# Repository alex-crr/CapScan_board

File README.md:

# CapScan 5x5

Bench readout board that scans a 5 TX x 5 RX printed skin sensor (reSkin / Skin-On) and returns the mutual capacitance of each taxel in pF. Sibling of [Muca_board](../Muca_board) (MUCA2), which returns raw FocalTech counts.

Status: rev 0.1. Schematic complete (ERC 0 errors). Board placed and fully routed (35/35 nets, KiCadRoutingTools checker: 0 violations, all nets connected). Still to do in KiCad: fill the B.Cu GND zone (press B), run KiCad's own DRC, silkscreen. Not fabricated.

## How it measures

One taxel at a time: the selected TX line is connected to the AD7746 excitation output (EXCA), the selected RX line to its input (CIN1+), and the 8 other lines are grounded. The AD7746 measures the floating capacitance between EXC and CIN; capacitance to ground is rejected (up to its 60 pF limit), so the grounded neighbours do not add to the reading.

| Block | Part | Notes |
|---|---|---|
| CDC | AD7746ARUZ (TSSOP-16) | 24-bit, +/-4.096 pF span around a CAPDAC offset of 0 to 17 pF, 11 to 109 ms per conversion, I2C 0x48. Internal reference; REFIN, VIN, CIN1-, CIN2, EXCB unused. |
| Line switches | 10x 74LVC1G3157 (SC-70-6) | One SPDT per line: B0 -> bus (EXC or CIN), B1 -> GND. |
| Reference | C8 2.2 pF C0G +/-0.05 pF (0402) + U14 74LVC1G3157 | C8 sits between EXC and CIN through its own switch, selected by IO1_5 (active low). Same bus and switch type as a taxel, so it checks gain including the CIN loading. |
| Select | PCA9555PW (TSSOP-24) | I2C 0x20. IO0_0-4 = TX1-5, IO1_0-4 = RX1-5, IO1_5 = reference. Select is active LOW. Power-up state is input with internal pull-up, so all lines are grounded until the firmware selects one. |
| Host | Seeed XIAO ESP32S3 (SMD) | USB-C and 3.3 V regulator on the module. |
| Power | XIAO 3V3 -> ferrite -> +3.3VA | +3.3VA feeds the AD7746 and the switches. |
| Sensor I/O | 2x 2.54 mm right-angle socket, 1x5 | J1 TX1-5, J2 RX1-5, same Clincher tail as MUCA2. |
| Grounding | H4 | Plated M3 hole on GND for a shield or the test fixture. H1-H3 are unplated. |
| Debug | PWR, HB, SENSE LEDs, 4-pin I2C header | J3: 3V3, GND, SDA, SCL. |

## XIAO pin map

| XIAO pin | GPIO | Function |
|---|---|---|
| D0 | GPIO1 | CDC_RDY (low when a conversion is ready) |
| D4 / D5 | GPIO5 / GPIO6 | SDA / SCL (default `Wire` pins), 2.2 kohm pull-ups |
| D8 / D9 | GPIO7 / GPIO8 | LED_HB / LED_SENSE (active high) |

## Scan sequence (firmware)

1. PCA9555: write output registers to 0xFF, then configure IO0_0-4 and IO1_0-5 as outputs.
2. For each taxel: clear the TX bit and the RX bit, wait about 1 ms, start a single conversion, wait for CDC_RDY, read 24 bits, set the two bits again.
3. C[pF] = (code - 0x800000) / 0x800000 * 4.096 + CAPDAC offset.

4. Calibration: with nothing selected, read the zero (board stray). Then clear only IO1_5 and read the reference: gain = C8 / (reference - zero). Repeat at the start of each session and when temperature changes.

A full 25-taxel frame takes about 0.3 s at the fastest setting and about 2.7 s at the lowest-noise one.

## Layout

48 x 47 mm, 2 layers, all parts on top, symmetric about the centre line. Top to bottom: sensor sockets (RX left, TX right), one switch directly under each socket pin with its row decoupling at both ends, AD7746 on the centre line between the two rows (CIN and EXC buses a few mm long), PCA9555 under the TX row, XIAO on the bottom edge with USB facing out, LEDs left of it and the I2C header right. The area under the RX row is left empty on purpose: it is the quiet zone around CIN.

## Open points

- Routing: sensor lines, GND vias, CIN/EXC buses and the reference branch are hand-laid (`tools/prelay.py`); the rest is autorouted with KiCadRoutingTools 0.24 (track 0.2 mm, power 0.3 mm, via 0.6/0.3 mm, clearance 0.15 mm requested, 0.144 mm minimum delivered, no via-in-pad). The autorouted part is functional, not pretty: the RX select lines cross the empty zone under the RX row on F.Cu, and select lines and +3.3VA cut the B.Cu plane in places.
- Rebuild order if the placement changes: `tools/place.py`, strip copper, `tools/prelay.py`, then route_planes.py (GND on B.Cu) and route.py with --keep-input-copper.
- CIN node capacitance to ground: about 18 pF (one switch on) + 5 x 6 pF (switches off) + traces + the sensor RX line to the grounded TX lines. The AD7746 limit is 60 pF. The switch values are from memory of the Nexperia datasheet: check them, and measure the gain error with a known C0G capacitor on a socket.
- C8 gives a repeatable reference, not a traceable one: its tolerance is 0.05 pF but the pads and the switch add stray of the same order. For absolute values, measure C8 in place once with an LCR meter (or compare with a known external C0G on a socket) and store that number.
- Taxel capacitance above 21 pF (17 pF CAPDAC + 4 pF) is out of range without the range-extension circuit of ADI CN-0552.
- No CAN (bench instrument). Add the MUCA2 CAN sheet if it has to go on a prosthesis.
- Silkscreen, 3D check of socket direction.

## Files

- `CapScan5x5.kicad_pro` - project (single A3 sheet)
- `CapScan.kicad_sym`, `CapScan.pretty/` - XIAO ESP32S3 symbol and footprint (copied from MUCA2)
- `tools/build_sch.py` - regenerates the schematic wiring and layout from `tools/base.placed` (run from this folder). Delete `tools/` once the schematic is edited by hand.

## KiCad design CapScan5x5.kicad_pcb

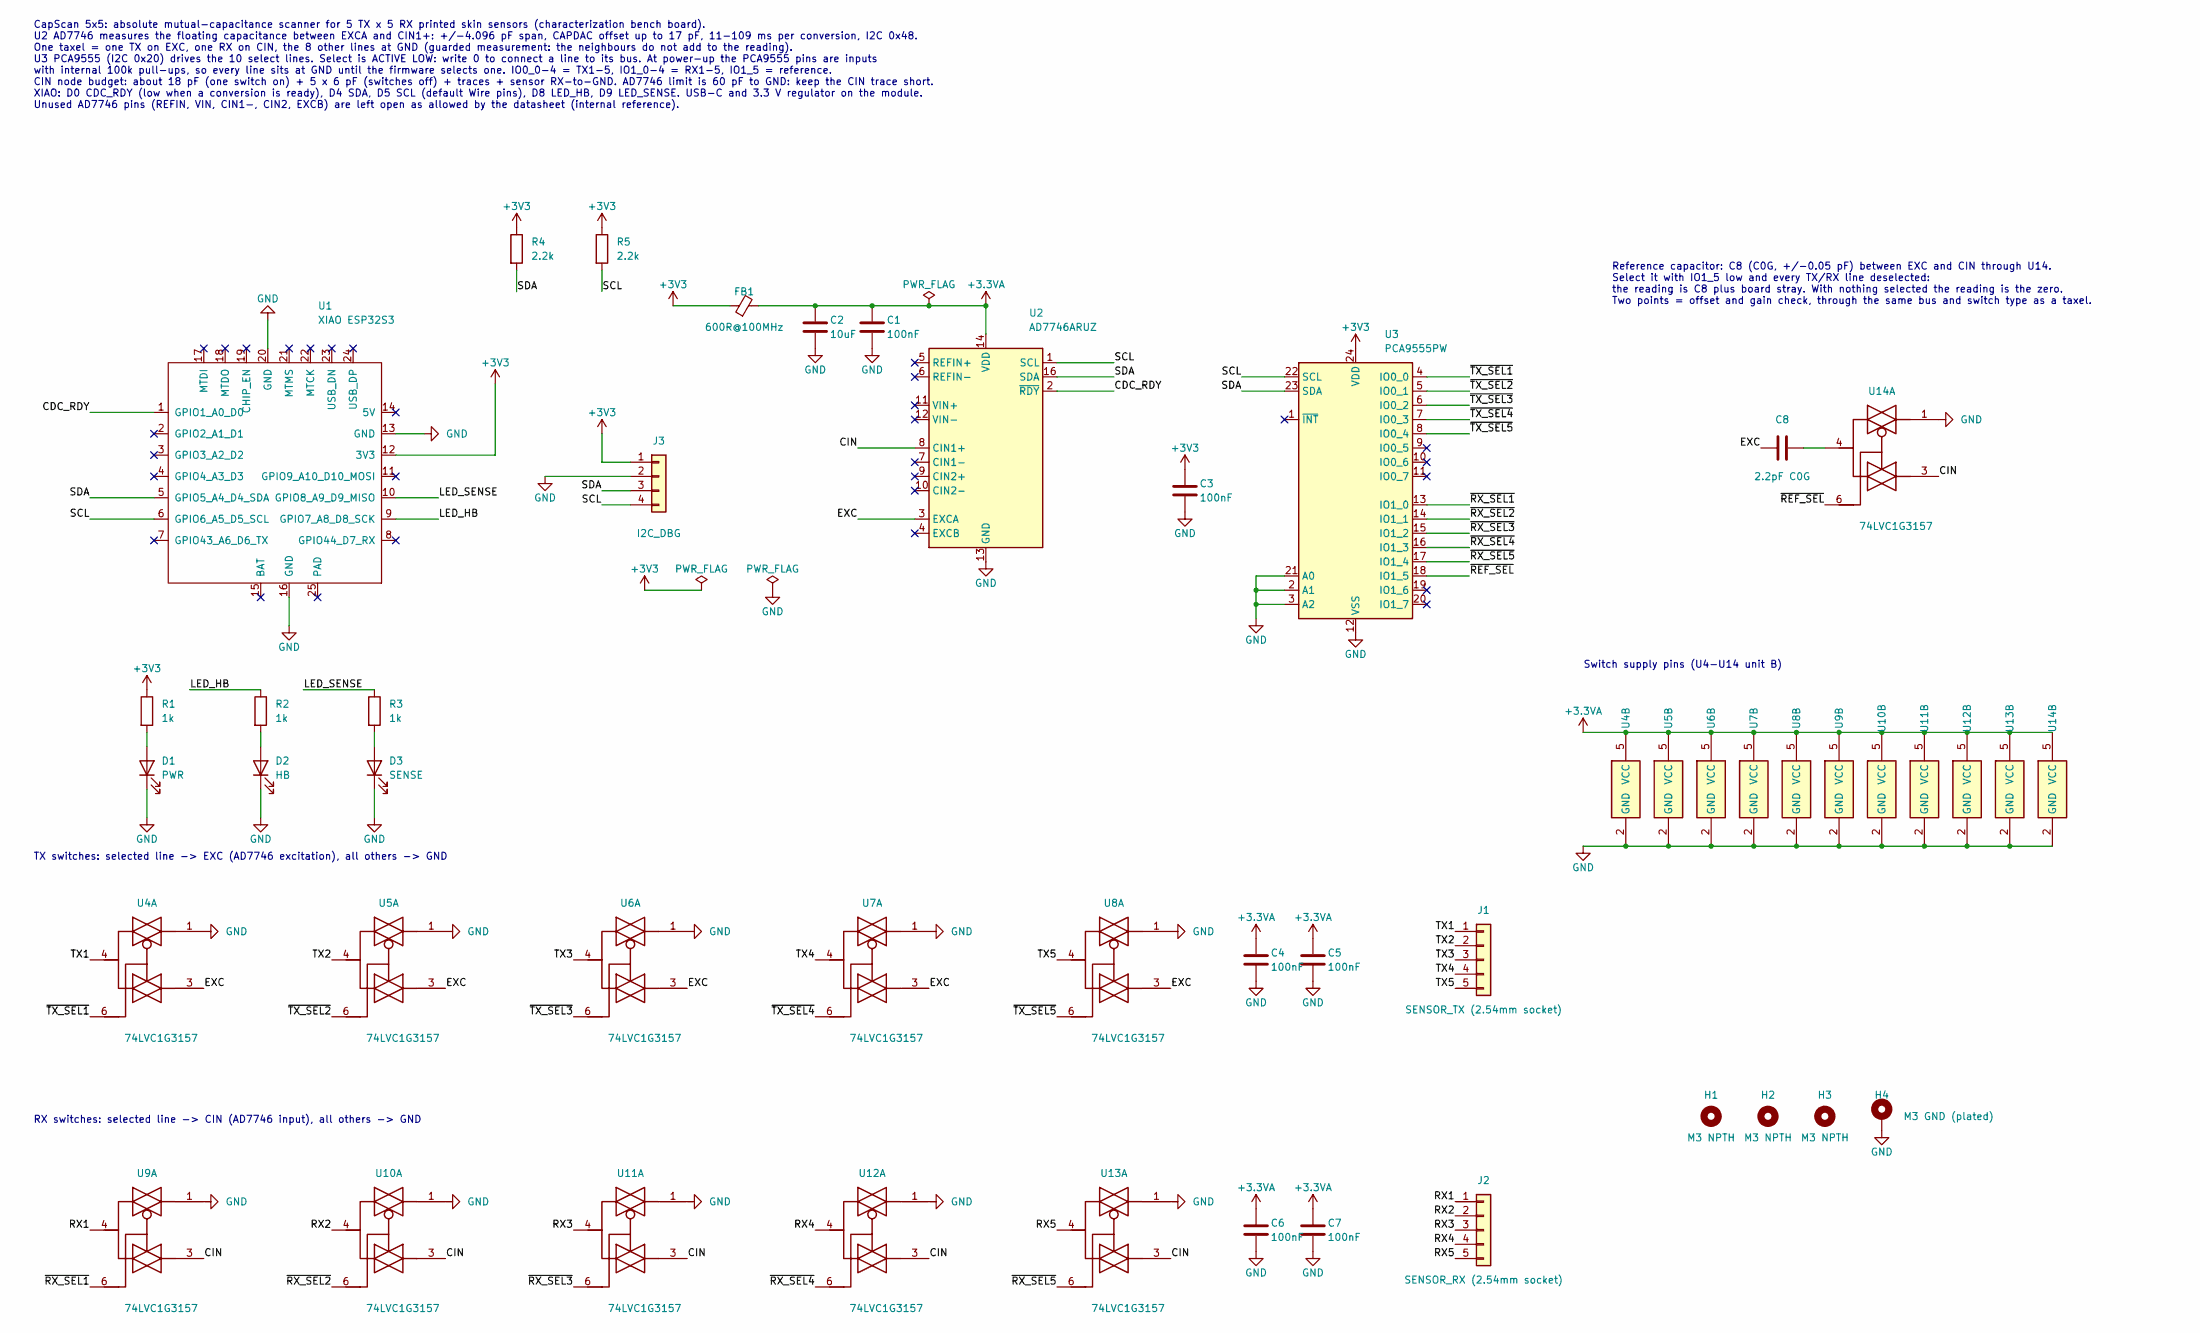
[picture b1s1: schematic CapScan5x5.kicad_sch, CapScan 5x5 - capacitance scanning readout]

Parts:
C1, C3, C4, C5, C6, C7: 100nF; C_0402_1005Metric
C2: 10uF; C_0603_1608Metric
C8: 2.2pF C0G; C_0402_1005Metric
D1: PWR; LED_0603_1608Metric
D2: HB; LED_0603_1608Metric
D3: SENSE; LED_0603_1608Metric
FB1: 600R@100MHz; L_0603_1608Metric
H1, H2, H3: M3 NPTH; MountingHole_3.2mm_M3
H4: M3 GND (plated); MountingHole_3.2mm_M3_Pad
J1: SENSOR_TX (2.54mm socket); PinSocket_1x05_P2.54mm_Horizontal
J2: SENSOR_RX (2.54mm socket); PinSocket_1x05_P2.54mm_Horizontal
J3: I2C_DBG; PinHeader_1x04_P2.54mm_Vertical
R1, R2, R3: 1k; R_0402_1005Metric
R4, R5: 2.2k; R_0402_1005Metric
U1: XIAO ESP32S3; XIAO-ESP32S3-SMD
U2: AD7746ARUZ; TSSOP-16_4.4x5mm_P0.65mm
U3: PCA9555PW; TSSOP-24_4.4x7.8mm_P0.65mm
U4, U5, U6, U7, U8, U9, U10, U11, U12, U13, U14: 74LVC1G3157; SOT-363_SC-70-6

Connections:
+3.3VA: C1.1, C2.1, C4.1, C5.1, C6.1, C7.1, FB1.2, U2.14 (VDD), U4.5 (VCC), U5.5 (VCC), U6.5 (VCC), U7.5 (VCC), U8.5 (VCC), U9.5 (VCC), U10.5 (VCC), U11.5 (VCC), U12.5 (VCC), U13.5 (VCC), U14.5 (VCC)
+3V3: C3.1, FB1.1, J3.1, R1.1, R4.1, R5.1, U1.12 (3V3), U3.24 (VDD)
CDC_RDY: U1.1 (GPIO1_A0_D0), U2.2 (~RDY)
CIN: U2.8 (CIN1+), U9.3, U10.3, U11.3, U12.3, U13.3, U14.3
EXC: C8.1, U2.3 (EXCA), U4.3, U5.3, U6.3, U7.3, U8.3
GND: C1.2, C2.2, C3.2, C4.2, C5.2, C6.2, C7.2, D1.1 (K), D2.1 (K), D3.1 (K), H4.1, J3.2, U1.13 (GND), U1.16 (GND), U1.20 (GND), U2.13 (GND), U3.2 (A1), U3.3 (A2), U3.12 (VSS), U3.21 (A0), U4.1, U4.2 (GND), U5.1, U5.2 (GND), U6.1, U6.2 (GND), U7.1, U7.2 (GND), U8.1, U8.2 (GND), U9.1, U9.2 (GND), U10.1, U10.2 (GND), U11.1, U11.2 (GND), U12.1, U12.2 (GND), U13.1, U13.2 (GND), U14.1, U14.2 (GND)
LED_HB: R2.1, U1.9 (GPIO7_A8_D8_SCK)
LED_SENSE: R3.1, U1.10 (GPIO8_A9_D9_MISO)
unnamed: C8.2, U14.4
unnamed: D1.2 (A), R1.2
unnamed: D2.2 (A), R2.2
unnamed: D3.2 (A), R3.2
RX1: J2.1, U9.4
RX2: J2.2, U10.4
RX3: J2.3, U11.4
RX4: J2.4, U12.4
RX5: J2.5, U13.4
SCL: J3.4, R5.2, U1.6 (GPIO6_A5_D5_SCL), U2.1 (SCL), U3.22 (SCL)
SDA: J3.3, R4.2, U1.5 (GPIO5_A4_D4_SDA), U2.16 (SDA), U3.23 (SDA)
TX1: J1.1, U4.4
TX2: J1.2, U5.4
TX3: J1.3, U6.4
TX4: J1.4, U7.4
TX5: J1.5, U8.4
~REF_SEL: U3.18 (IO1_5), U14.6
~RX_SEL1: U3.13 (IO1_0), U9.6
~RX_SEL2: U3.14 (IO1_1), U10.6
~RX_SEL3: U3.15 (IO1_2), U11.6
~RX_SEL4: U3.16 (IO1_3), U12.6
~RX_SEL5: U3.17 (IO1_4), U13.6
~TX_SEL1: U3.4 (IO0_0), U4.6
~TX_SEL2: U3.5 (IO0_1), U5.6
~TX_SEL3: U3.6 (IO0_2), U6.6
~TX_SEL4: U3.7 (IO0_3), U7.6
~TX_SEL5: U3.8 (IO0_4), U8.6

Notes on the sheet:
Switch supply pins (U4-U14 unit B)
Reference capacitor: C8 (C0G, +/-0.05 pF) between EXC and CIN through U14. Select it with IO1_5 low and every TX/RX line deselected: the reading is C8 plus board stray. With nothing selected the reading is the zero. Two points = offset and gain check, through the same bus and switch type as a taxel.
TX switches: selected line -> EXC (AD7746 excitation), all others -> GND
RX switches: selected line -> CIN (AD7746 input), all others -> GND
CapScan 5x5: absolute mutual-capacitance scanner for 5 TX x 5 RX printed skin sensors (characterization bench board). U2 AD7746 measures the floating capacitance between EXCA and CIN1+: +/-4.096 pF span, CAPDAC offset up to 17 pF, 11-109 ms per conversion, I2C 0x48. One taxel = one TX on EXC, one R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

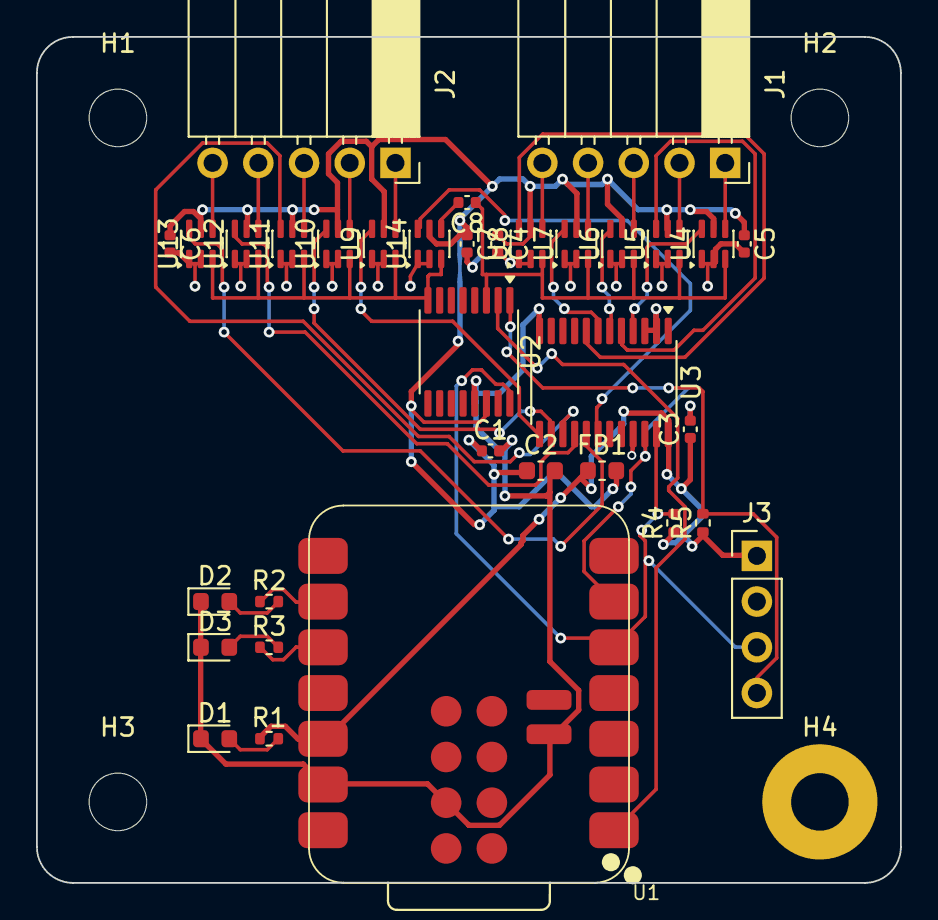
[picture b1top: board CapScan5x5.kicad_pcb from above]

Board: 2 copper layers, 48.0 x 47.0 mm, 38 parts (0 on the bottom side), 35 nets.

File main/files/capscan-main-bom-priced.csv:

Designators,Value,Footprint,Qty/Board,LCSC Part #,JLC Type,JLC Stock,LCSC Stock,Unit @1bd (USD),Unit @5bd (USD),Unit @10bd (USD),Unit @50bd (USD),MPN,Datasheet
"C1,C3,C4,C5,C6,C7",100nF,C_0402_1005Metric,6,,Missing,,,,,,,,
C2,10uF,C_0603_1608Metric,1,,Missing,,,,,,,,
C8,2.2pF C0G,C_0402_1005Metric,1,,Missing,,,,,,,,
D1,PWR,LED_0603_1608Metric,1,,Missing,,,,,,,,
D2,HB,LED_0603_1608Metric,1,,Missing,,,,,,,,
D3,SENSE,LED_0603_1608Metric,1,,Missing,,,,,,,,
FB1,600R@100MHz,L_0603_1608Metric,1,,Missing,,,,,,,,
J1,SENSOR_TX (2.54mm socket),PinSocket_1x05_P2.54mm_Horizontal,1,,Missing,,,,,,,,
J2,SENSOR_RX (2.54mm socket),PinSocket_1x05_P2.54mm_Horizontal,1,,Missing,,,,,,,,
J3,I2C_DBG,PinHeader_1x04_P2.54mm_Vertical,1,,Missing,,,,,,,,
"R1,R2,R3",1k,R_0402_1005Metric,3,,Missing,,,,,,,,
"R4,R5",2.2k,R_0402_1005Metric,2,,Missing,,,,,,,,
U1,XIAO ESP32S3,XIAO-ESP32S3-SMD,1,,Missing,,,,,,,,
U2,AD7746ARUZ,TSSOP-16_4.4x5mm_P0.65mm,1,,Missing,,,,,,,,https://www.analog.com/media/en/technical-documentation/data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
U3,PCA9555PW,TSSOP-24_4.4x7.8mm_P0.65mm,1,,Missing,,,,,,,,https://www.nxp.com/docs/en/data-sheet/PCA9555.pdf
"U4,U5,U6,U7,U8,U9,U10,U11,U12,U13,U14",74LVC1G3157,SOT-363_SC-70-6,11,,Missing,,,,,,,,http://www.ti.com/lit/sg/scyt129e/scyt129e.pdf

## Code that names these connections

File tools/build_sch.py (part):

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# ---- LEDs
for x in (40.64, 60.96, 81.28):
    s.wire((x, 147.32), (x, 149.86)); s.wire((x, 157.48), (x, 162.56))
s.wire((48.26, 139.7), (60.96, 139.7)); s.label('LED_HB', 48.26, 139.7, 0)
s.wire((68.58, 139.7), (81.28, 139.7)); s.label('LED_SENSE', 68.58, 139.7, 0)
# ---- I2C pull-ups, debug header
s.wire((106.68, 64.77), (106.68, 68.58)); s.label('SDA', 106.68, 68.58, 0)
s.wire((121.92, 64.77), (121.92, 68.58)); s.label('SCL', 121.92, 68.58, 0)
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s.wire((149.86, 71.12), (190.5, 71.12), (190.5, 76.2))
# ---- AD7746
for y in (81.28, 83.82, 88.9, 91.44, 99.06, 101.6, 104.14, 111.76): s.ncf(177.8, y)
s.wire((177.8, 96.52), (167.64, 96.52)); s.label('CIN', 167.64, 96.52, 180)
s.wire((177.8, 109.22), (167.64, 109.22)); s.label('EXC', 167.64, 109.22, 180)
for y, nm in ((81.28, 'SCL'), (83.82, 'SDA'), (86.36, 'CDC_RDY')):
    s.wire((203.2, y), (213.36, y)); s.label(nm, 213.36, y, 0)
# ---- PCA9555
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    y = 83.82 + 2.54 * k; s.wire((269.24, y), (276.86, y)); s.label('~{TX_SEL%d}' % (k + 1), 276.86, y, 0)
    y = 106.68 + 2.54 * k; s.wire((269.24, y), (276.86, y)); s.label('~{RX_SEL%d}' % (k + 1), 276.86, y, 0)
for y in (96.52, 99.06, 101.6, 121.92, 124.46): s.ncf(269.24, y)
s.wire((269.24, 119.38), (276.86, 119.38)); s.label('~{REF_SEL}', 276.86, 119.38, 0)
# ---- reference branch
s.field('U14', 'Reference', 350.52, 86.36); s.field('U14', 'Value', 353.06, 110.49)
s.field('C8', 'Reference', 332.74, 91.44, ang=90); s.field('C8', 'Value', 332.74, 101.6, ang=90)
s.label('EXC', 328.93, 96.52, 180); s.wire((336.55, 96.52), (340.36, 96.52))
s.label('~{REF_SEL}', 340.36, 106.68, 180); s.label('CIN', 360.68, 101.6, 0)
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
s.text('TX switches: selected line -> EXC (AD7746 excitation), all others -> GND', 20.32, 168.91)
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 'U3 PCA9555 (I2C 0x20) drives the 10 select lines. Select is ACTIVE LOW: write 0 to connect a line to its bus. At power-up the PCA9555 pins are inputs\n'
 'with internal 100k pull-ups, so every line sits at GND until the firmware selects one. IO0_0-4 = TX1-5, IO1_0-4 = RX1-5, IO1_5 = reference.\n'
 'CIN node budget: about 18 pF (one switch on) + 5 x 6 pF (switches off) + traces + sensor RX-to-GND. AD7746 limit is 60 pF to GND: keep the CIN trace short.\n'
 'XIAO: D0 CDC_RDY (low when a conversion is ready), D4 SDA, D5 SCL (default Wire pins), D8 LED_HB, D9 LED_SENSE. USB-C and 3.3 V regulator on the module.\n'
 'Unused AD7746 pins (REFIN, VIN, CIN1-, CIN2, EXCB) are left open as allowed by the datasheet (internal reference).', 20.32, 20.32)

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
